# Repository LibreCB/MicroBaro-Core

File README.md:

# µBaro Core

A small and cheap device able to log data from the integrated BMI160 6-DOF IMU and BMP390 barometer to an SD card.
It also includes two GPIOs that can be used to record additional data, or trigger actions.

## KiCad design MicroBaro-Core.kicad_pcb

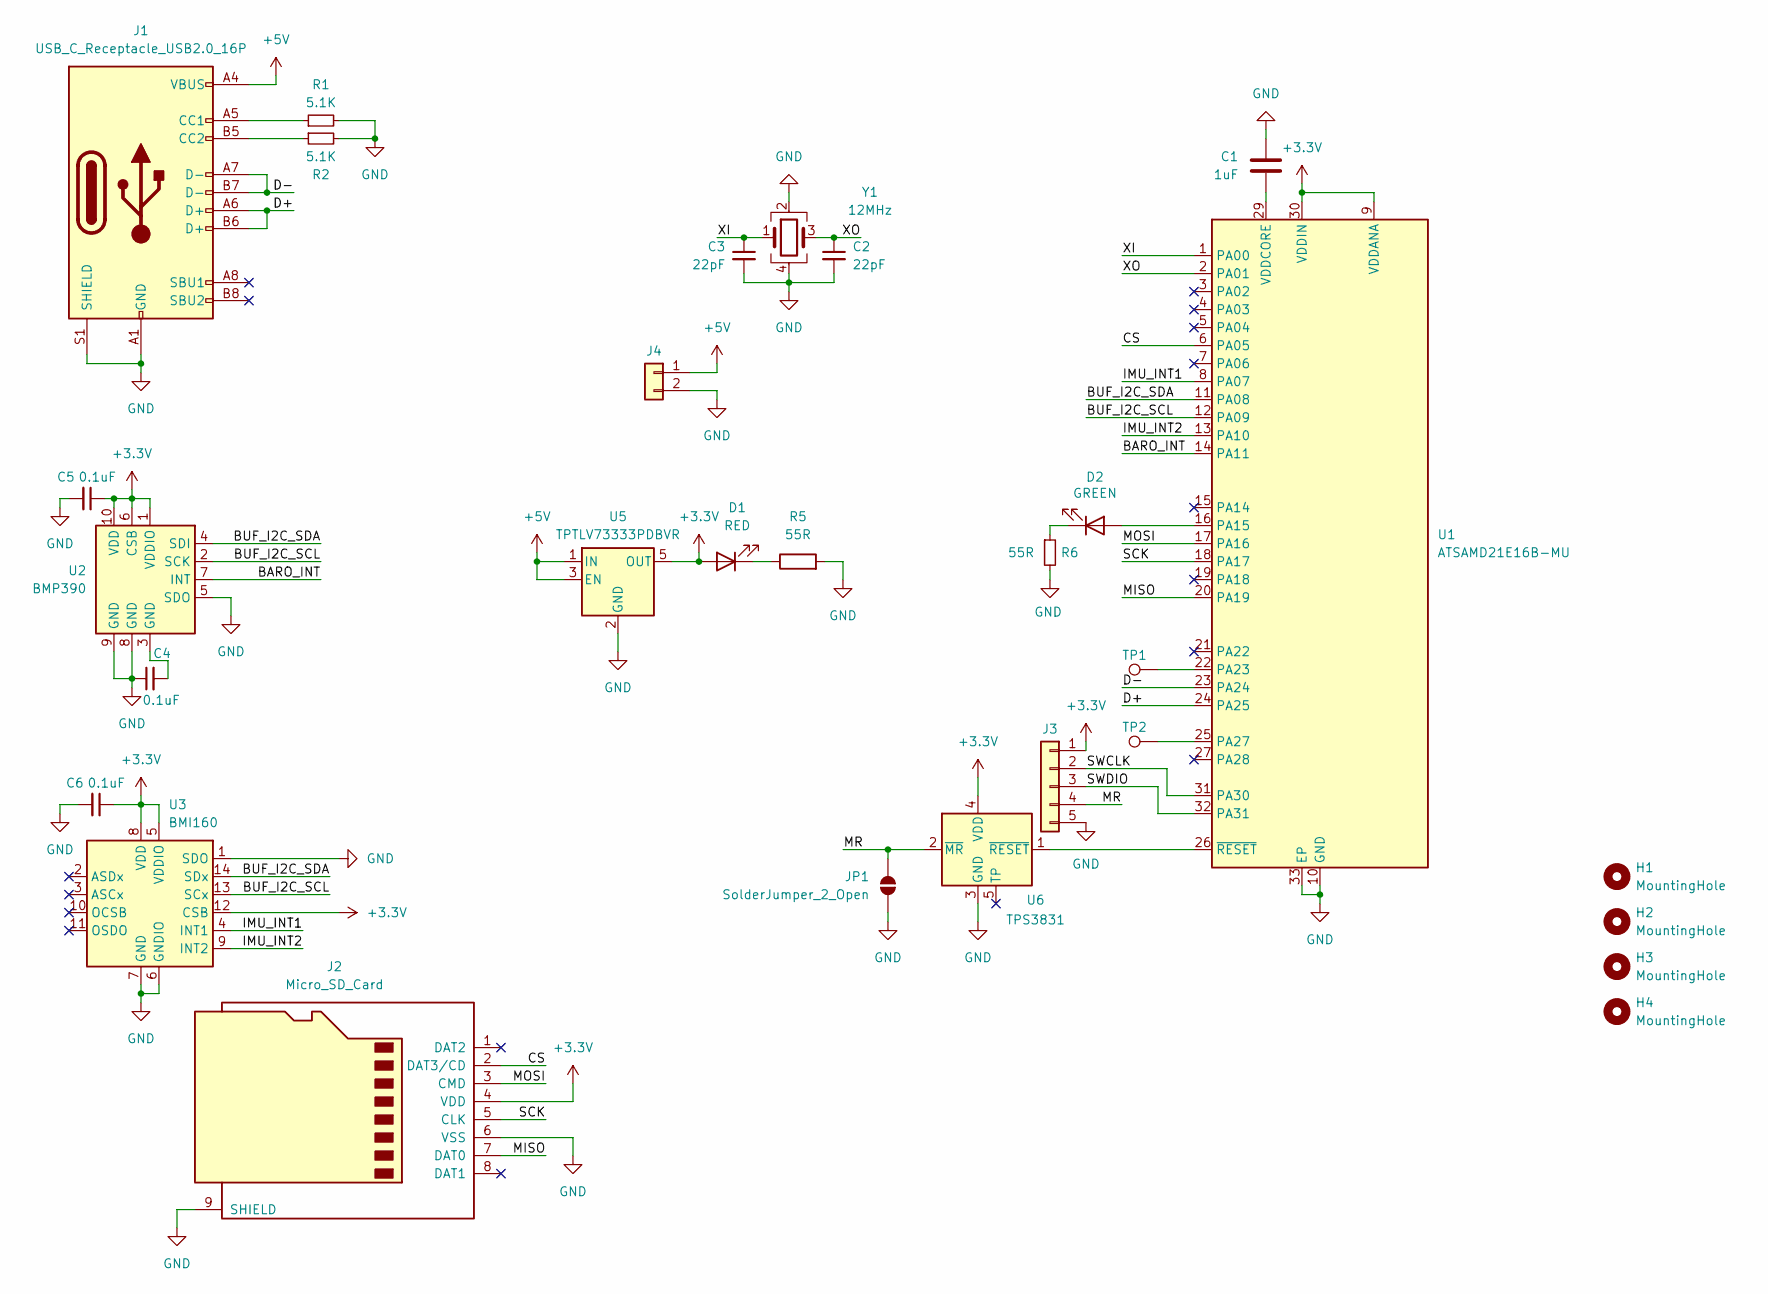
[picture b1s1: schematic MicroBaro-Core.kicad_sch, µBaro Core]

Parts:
C1: 1uF; C_0603_1608Metric; MPN CL10B105KP8NNNC; LCSC Part # C1525
C2, C3: 22pF; C_0603_1608Metric; MPN CL10C220JB8NFNC; LCSC Part # C1555
C4, C5, C6: 0.1uF; C_0603_1608Metric; MPN CL10B104KB8NNWC; LCSC Part # C1591
D1: RED; LED_0603_1608Metric; MPN LTST-C191KRKT; LCSC Part # C2286
D2: GREEN; LED_0603_1608Metric; MPN LTST-C190KGKT; LCSC Part # C12624
H1, H2, H3, H4: MountingHole; MountingHole_2.2mm_M2
J1: USB_C_Receptacle_USB2.0_16P; USB_C_Receptacle_GCT_USB4105-xx-A_16P_TopMnt_Horizontal; MPN USB4105-GF-A; LCSC Part # C3025063
J2: Micro_SD_Card; TF-SMD_TF-015; MPN MSD-4-A; LCSC Part # C113206
J3: Conn_01x04; PinHeader_1x05_P2.54mm_Vertical
J4: Conn_01x02; JST_PH_B2B-PH-K_1x02_P2.00mm_Vertical; MPN B2B-PH-K-S; LCSC Part # C131337
JP1: SolderJumper_2_Open; SolderJumper-2_P1.3mm_Open_RoundedPad1.0x1.5mm
R1, R2: 5.1K; R_0603_1608Metric; MPN SR0603JR-7T5K1L; LCSC Part # C25905
R5, R6: 55R; R_0603_1608Metric; MPN RC0603FR-0756RL; LCSC Part # C137957
TP1, TP2: TestPoint; TestPoint_Pad_D2.0mm
U1: ATSAMD21E16B-MU; QFN-32-1EP_5x5mm_P0.5mm_EP3.6x3.6mm; MPN ATSAMD21E16B-MU; LCSC Part # C614241
U2: BMP390; Bosch_WFLGA-10_2x2mm_P0.5mm; MPN BMP390; LCSC Part # C2684802
U3: BMI160; Bosch_LGA-14_3x2.5mm_P0.5mm; MPN BMI270; LCSC Part # C94021
U5: TPTLV73333PDBVR; SOT-23-5; MPN TLV73333PDBVR; LCSC Part # C2937043
U6: TPS3831; Texas_X2SON-4_1x1mm_P0.65mm; MPN TPS3831K33DQNR; DigiKey Part # 296-40752-1-ND
Y1: 12MHz; Crystal_SMD_3225-4Pin_3.2x2.5mm; MPN 403I35D12M00000; LCSC Part # C9002

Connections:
+3.3V: C5.1, C6.1, D1.2 (A), J2.4 (VDD), J3.1, U1.9 (VDDANA), U1.30 (VDDIN), U2.1 (VDDIO), U2.6 (CSB), U2.10 (VDD), U3.5 (VDDIO), U3.8 (VDD), U3.12 (CSB), U5.5 (OUT), U6.4 (VDD)
+5V: J1.A4 (VBUS), J1.A9 (VBUS), J1.B4 (VBUS), J1.B9 (VBUS), J4.1, U5.1 (IN), U5.3 (EN)
/BARO_INT: U1.14 (PA11), U2.7 (INT)
/BUF_I2C_SCL: U1.12 (PA09), U2.2 (SCK), U3.13 (SCx)
/BUF_I2C_SDA: U1.11 (PA08), U2.4 (SDI), U3.14 (SDx)
/CS: J2.2 (DAT3/CD), U1.6 (PA05)
/D+: J1.A6 (D+), J1.B6 (D+), U1.24 (PA25)
/D-: J1.A7 (D-), J1.B7 (D-), U1.23 (PA24)
/IMU_INT1: U1.8 (PA07), U3.4 (INT1)
/IMU_INT2: U1.13 (PA10), U3.9 (INT2)
/MISO: J2.7 (DAT0), U1.20 (PA19)
/MOSI: J2.3 (CMD), U1.17 (PA16)
/MR: J3.4, JP1.2 (B), U6.2 (~MR)
/SCK: J2.5 (CLK), U1.18 (PA17)
/SWCLK: J3.2, U1.31 (PA30)
/SWDIO: J3.3, U1.32 (PA31)
/XI: C3.1, U1.1 (PA00), Y1.1
/XO: C2.1, U1.2 (PA01), Y1.3
GND: C1.1, C2.2, C3.2, C4.1, C5.2, C6.2, J1.A1 (GND), J1.A12 (GND), J1.B1 (GND), J1.B12 (GND), J1.S1 (SHIELD), J2.6 (VSS), J2.9 (SHIELD), J3.5, J4.2, JP1.1 (A), R1.2, R2.2, R5.2, R6.2, U1.10 (GND), U1.28 (GND), U1.33 (EP), U2.5 (SDO), U2.8 (GND), U2.9 (GND), U3.1 (SDO), U3.6 (GNDIO), U3.7 (GND), U5.2 (GND), U6.3 (GND), Y1.2, Y1.4
unnamed: C4.2, U2.3 (GND)
unnamed: D1.1 (K), R5.1
unnamed: D2.2 (A), U1.16 (PA15)
unnamed: D2.1 (K), R6.1
unnamed: J1.A5 (CC1), R1.1
unnamed: J1.B5 (CC2), R2.1
unnamed: TP1.1, U1.22 (PA23)
unnamed: TP2.1, U1.25 (PA27)
unnamed: C1.2, U1.29 (VDDCORE)
unnamed: U1.26 (~RESET), U6.1 (~RESET)

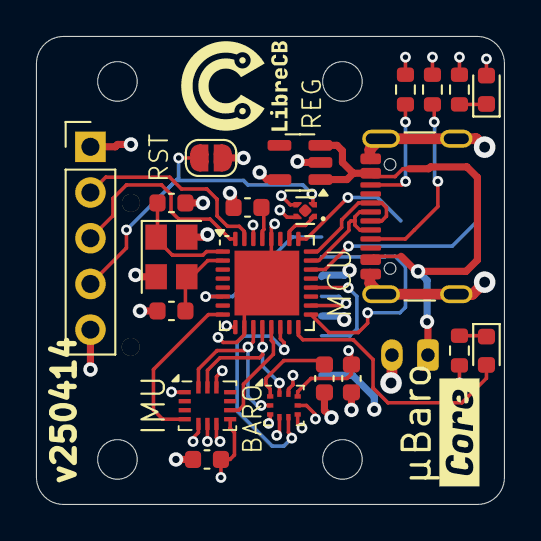
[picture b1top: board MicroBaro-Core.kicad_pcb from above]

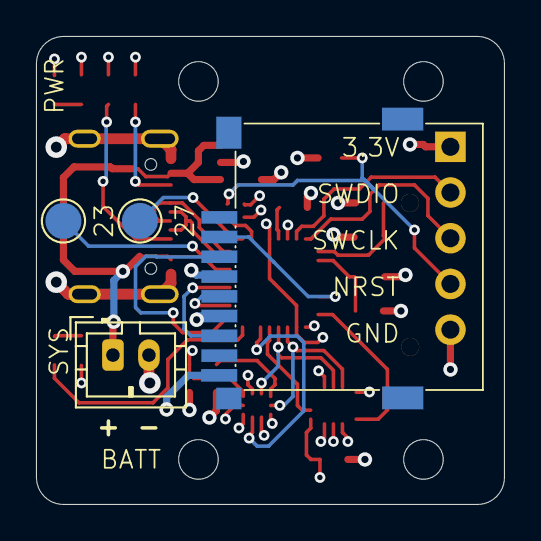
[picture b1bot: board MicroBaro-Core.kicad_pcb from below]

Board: 4 copper layers, 26.0 x 26.0 mm, 30 parts (4 on the bottom side), 29 nets.

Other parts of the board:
kibuzzard-67E48EA0: G***; kibuzzard-67E48EA0

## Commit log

2025-03-27 Initial Revision
2025-03-27 Add render workflow
2025-03-27 Allow manually triggering the PCB render workflow
2025-03-27 fix dispatch typo
2025-03-27 Add revision to PCB
2025-03-27 Install KiCad
2025-03-27 Clean before rendering images
2025-03-27 Used cache when installing kicad
2025-03-27 Fix permissions
2025-03-27 Render PCB
2025-03-27 Create basic README
2025-03-27 Generate upside down read view
2025-03-27 Add crystal
2025-03-27 Add missing JST part number
2025-03-29 add digikey part numbers
2025-04-08 fix schematic
2025-04-08 Add BMP390 symbols
2025-04-08 Fix wrong footprint on barometer
2025-04-08 Cleanup workflow
2025-04-08 Ignore gitignore for renders
2025-04-08 Fix typo in image name
2025-04-08 Cache fonts
2025-04-09 Use local 3D model for MCU
2025-04-09 Clone repository if not in cache
2025-04-09 Use shallow clone
2025-04-09 Cleanup some routing
2025-04-09 Do not install fonts
2025-04-12 Next revision
2025-04-13 Fix git diff (again)
